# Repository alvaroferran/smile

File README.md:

# Smile
The tablet that turns to follow your face as you move. 

---

It uses OpenCV's haarcascade to find front-facing faces and communicates over bluetooth with an arduino to move itself around.

[This wheel](https://github.com/bq/mechatronics/tree/master/wheels/clippableWheel) is used to as the stand to move the tablet.

Note: This will NOT work unless you change the variable "address" in the Android MainActivity.java file to match your own bluetooth module's MAC address.

Attributions
--------------------------------------------------------------
 - [Alvaro Ferrán Cifuentes](https://github.com/alvaroferran)
  - Android app, PCB design

 - [Pighixxx](http://www.pighixxx.com/test/)
  - Orginal idea, PCB design

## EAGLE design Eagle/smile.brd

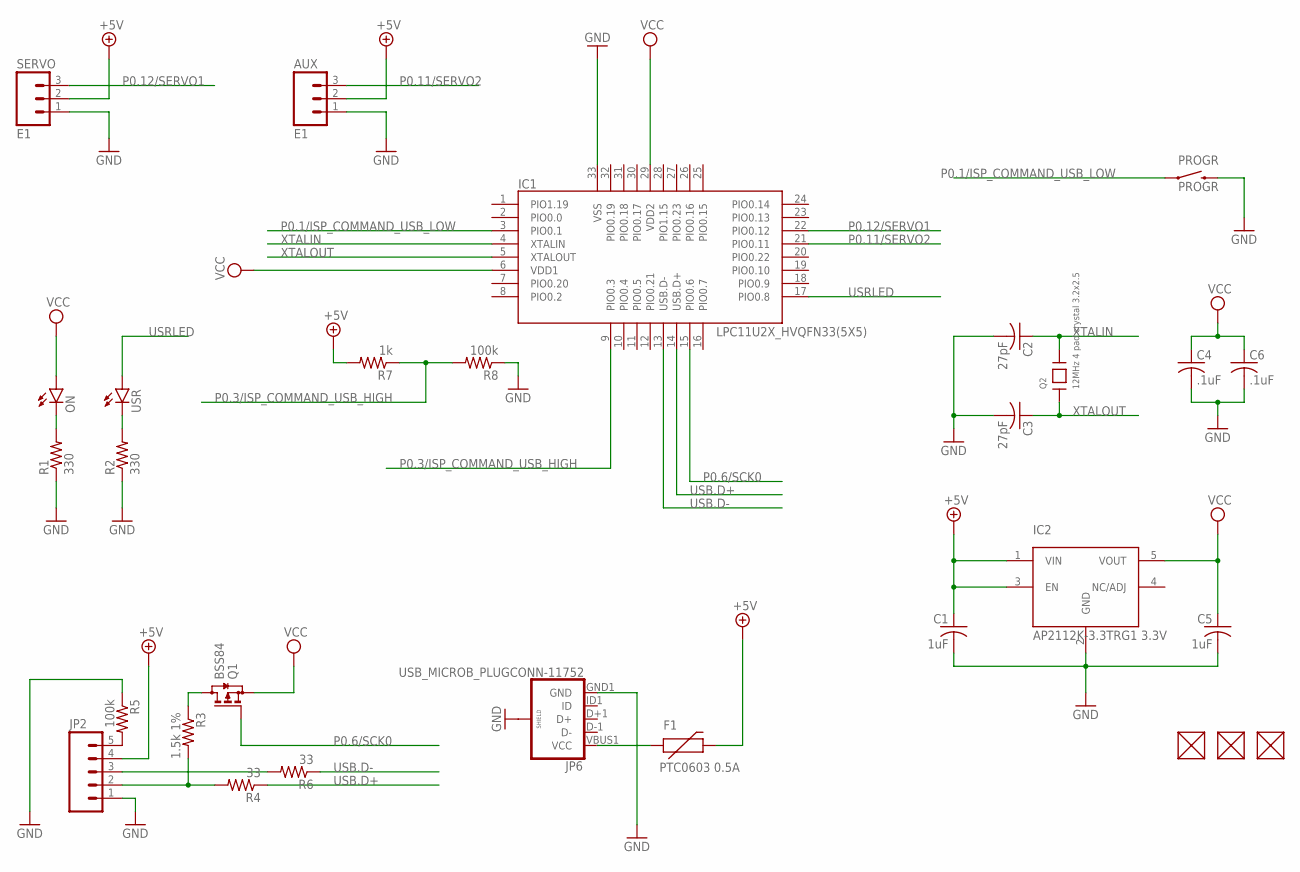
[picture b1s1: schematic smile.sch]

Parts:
AUX: E1; 1X03_NO_SILK
C1, C5: 1uF; C0603K
C2, C3: 27pF; C0402K
C4, C6: .1uF; C0402K
F1: PTC0603 0.5A; 0603
FUD1, FUD2, FUD3: FIDUCIAL; FIDUCIAL_40MIL
IC1: LPC11U2X_HVQFN33(5X5); HVQFN33_5X5MM
IC2: AP2112K-3.3TRG1 3.3V; SOT23-5
JP2: M05LOCK; 1X05_LOCK
JP6: USB_MICROB_PLUGCONN-11752; USB-B-MICRO-SMD_V03
ON: LED0603; LED-0603
PROGR: PROGR; TACTILE-PTH-SIDEEZ
Q1: BSS84; SOT23
Q2: 12MHz 4 pad crystal 3.2x2.5; CRYSTAL_3.2X2.5
R1, R2: 330; 0402-RES
R3: 1.5k 1%; R0402
R4, R6: 33; R0402
R5, R8: 100k; R0402
R7: 1k; R0402
SERVO: E1; 1X03_NO_SILK
USR: LED0603; LED-0603

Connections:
+5V: AUX.2, C1.1, F1.2, IC2.1 (VIN), IC2.3 (EN), JP2.4, R7.2, SERVO.2
GND: AUX.1, C1.2, C2.2, C3.2, C4.2, C5.2, C6.2, IC1.33 (VSS), IC2.2 (GND), JP2.1, JP6.GND1 (GND), JP6.SHIELD1 (SHIELD), JP6.SHIELD2 (SHIELD), JP6.SHIELD3 (SHIELD), PROGR.2, R1.1, R2.1, R5.1, R8.1, SERVO.1
unnamed: JP2.3, R6.2
unnamed: ON.C, R1.2
unnamed: JP2.2, R3.2, R4.2
unnamed: Q1.3 (D), R3.1
unnamed: F1.1, JP6.VBUS1 (VCC)
unnamed: JP2.5, R5.2
unnamed: R2.2, USR.C
P0.1/ISP_COMMAND_USB_LOW: IC1.3 (PIO0.1), PROGR.1
P0.3/ISP_COMMAND_USB_HIGH: IC1.9 (PIO0.3), R7.1, R8.2
P0.6/SCK0: IC1.15 (PIO0.6), Q1.1 (G)
P0.11/SERVO2: AUX.3, IC1.21 (PIO0.11)
P0.12/SERVO1: IC1.22 (PIO0.12), SERVO.3
USB.D+: IC1.14 (USB.D+), R4.1
USB.D-: IC1.13 (USB.D-), R6.1
USRLED: IC1.17 (PIO0.8), USR.A
VCC: C4.1, C5.1, C6.1, IC1.6 (VDD1), IC1.29 (VDD2), IC2.5 (VOUT), ON.A, Q1.2 (S)
XTALIN: C2.1, IC1.4 (XTALIN), Q2.3
XTALOUT: C3.1, IC1.5 (XTALOUT), Q2.1

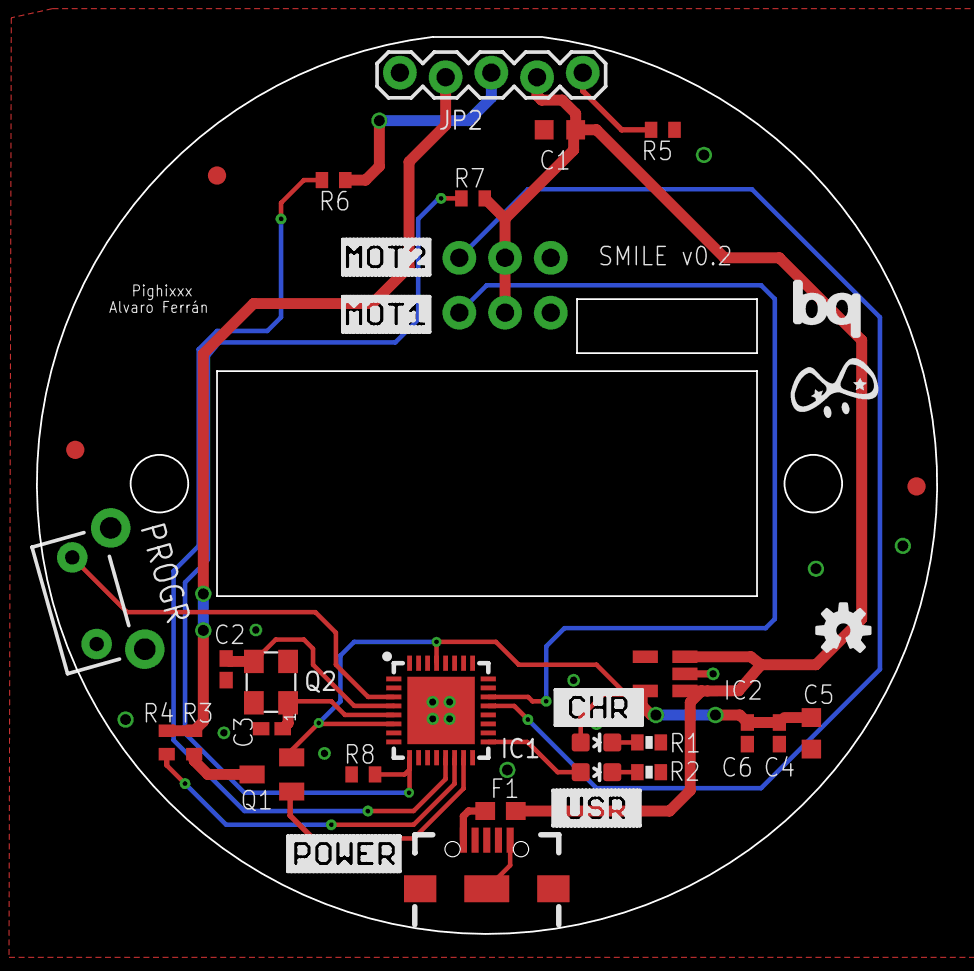
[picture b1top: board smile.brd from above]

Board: 2 copper layers, 50.0 x 49.8 mm, 37 parts (0 on the bottom side), 20 nets.

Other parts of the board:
U$1: OSHW-LOGO-S
U$2: SYM_PIGHIXXX
U$3: BQ_LOGO_MEDIUM
U$4: S_MOT1
U$5: S_MOT2
U$6: S_USR
U$7: S_CHR
U$8: S_POWER

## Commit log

2015-07-02 Android app, Arduino code, Eagle files added

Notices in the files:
parts and their libraries:
SparkFun-PowerIC: Licensing: Creative Commons ShareAlike 4.0 International - https://creativecommons.org/licenses/by-sa/4.0
